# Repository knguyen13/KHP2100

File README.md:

# KHP2100

Description:
Interact with LEDs through mechanical switches.

Features a 2-layer board with a 5V LDO regulator, atmega328p MCU, push-buttons, leds, and supporting components.
Mode button with a hardware trigger(interrupt) to switch between different game modes. 
ICSP connection to MCU for reprogrammability.

Archived 02/08/2022

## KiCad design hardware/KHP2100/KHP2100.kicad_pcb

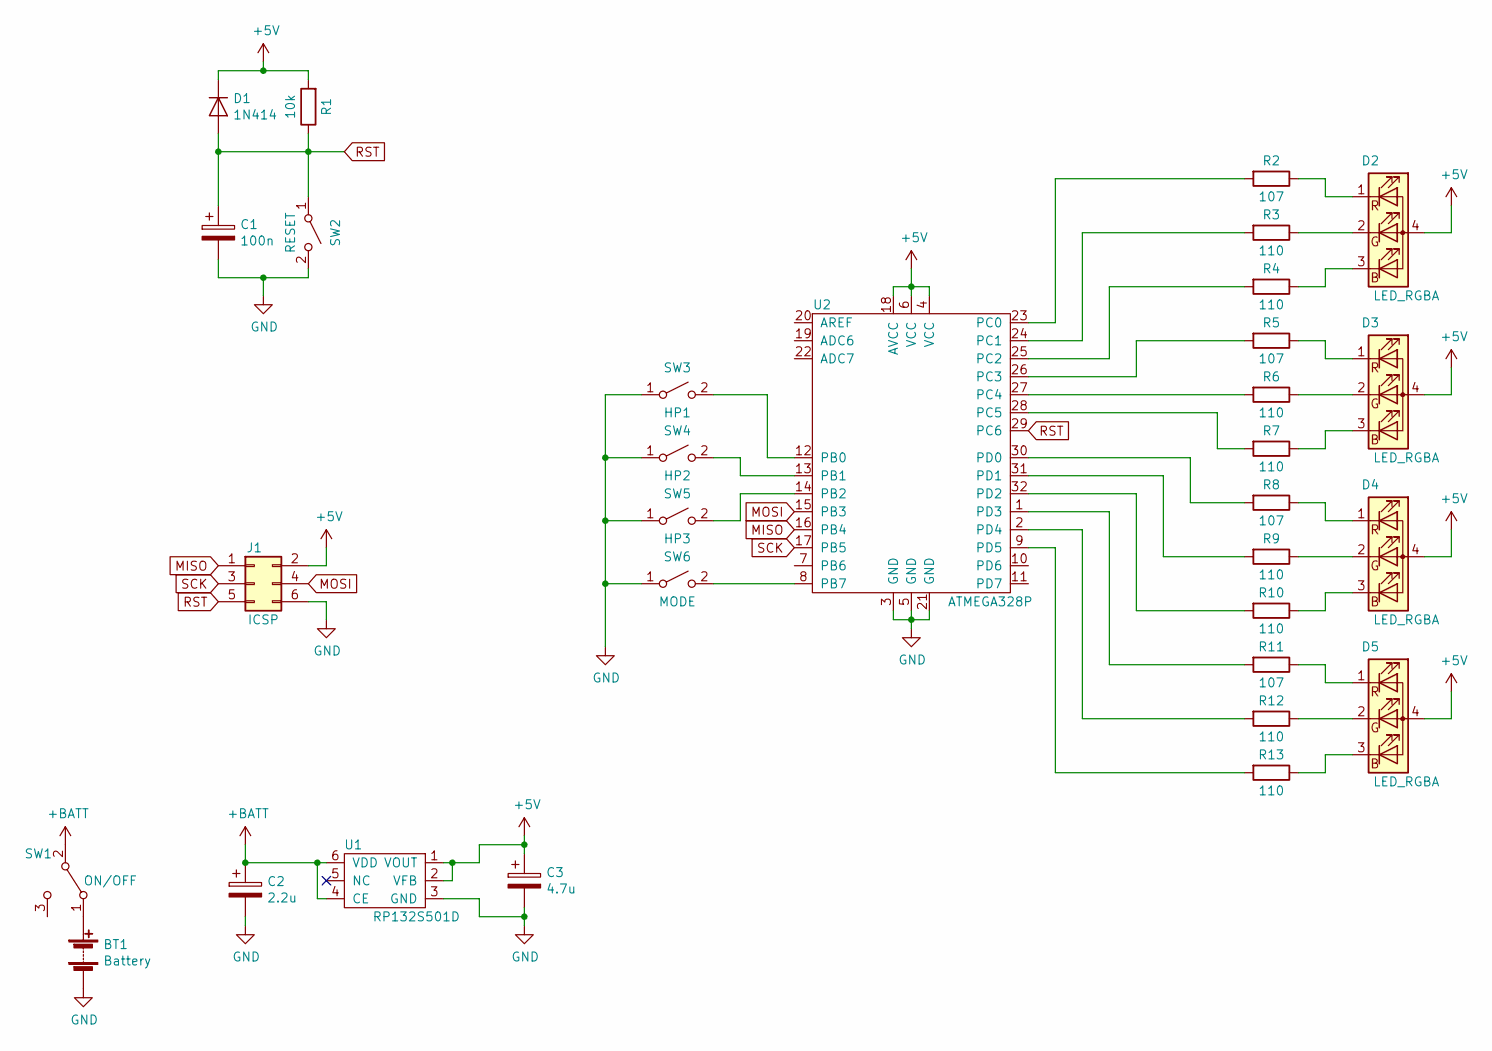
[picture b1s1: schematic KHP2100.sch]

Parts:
BT1: Battery; BH800S
C1: 100n; C_0603_1608Metric_Pad1.05x0.95mm_HandSolder
C2: 2.2u; C_0603_1608Metric_Pad1.05x0.95mm_HandSolder
C3: 4.7u; C_0603_1608Metric_Pad1.05x0.95mm_HandSolder
D1: 1N414; D_SOD-123
D2, D3, D4, D5: LED_RGBA; RGB_LED_0606_1616METRIC
J1: ICSP
R1: 10k; R_0603_1608Metric_Pad1.05x0.95mm_HandSolder
R2, R5, R8, R11: 107; R_1206_3216Metric_Pad1.42x1.75mm_HandSolder
R3, R4, R6, R7, R9, R10, R12, R13: 110; R_0805_2012Metric_Pad1.15x1.40mm_HandSolder
SW1: ON/OFF; CJS1200A
SW2: RESET; EVQ-Q2Y03W
SW3: HP1; MX_SWITCH
SW4: HP2; MX_SWITCH
SW5: HP3; MX_SWITCH
SW6: MODE; EVQ-Q2Y03W
U1: RP132S501D
U2: ATMEGA328P

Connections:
+5V: C3.1, D1.1 (K), D2.4 (A), D3.4 (A), D4.4 (A), D5.4 (A), J1.2, R1.2, U1.1 (VOUT), U1.2 (VFB), U2.4 (VCC), U2.6 (VCC), U2.18 (AVCC)
+BATT: C2.1, SW1.2 (B), U1.4 (CE), U1.6 (VDD); also elsewhere on the board
GND: BT1.2 (-), C1.2, C2.2, C3.2, J1.6, SW2.2 (B), SW3.1 (A), SW4.1 (A), SW5.1 (A), SW6.1 (A), U1.3 (GND), U2.3 (GND), U2.5 (GND), U2.21 (GND); also elsewhere on the board
MISO: J1.1, U2.16 (PB4)
MOSI: J1.4, U2.15 (PB3)
unnamed 5: BT1.1 (+), SW1.1 (A); also elsewhere on the board
unnamed: D2.1 (RK), R2.1
unnamed: D2.2 (GK), R3.1
unnamed: D2.3 (BK), R4.1
unnamed: D3.1 (RK), R5.1
unnamed: D3.2 (GK), R6.1
unnamed: D3.3 (BK), R7.1
unnamed: D4.1 (RK), R8.1
unnamed: D4.2 (GK), R9.1
unnamed: D4.3 (BK), R10.1
unnamed: D5.1 (RK), R11.1
unnamed: D5.2 (GK), R12.1
unnamed: D5.3 (BK), R13.1
unnamed: R2.2, U2.23 (PC0)
unnamed: R3.2, U2.24 (PC1)
unnamed: R4.2, U2.25 (PC2)
unnamed: R5.2, U2.26 (PC3)
unnamed: R6.2, U2.27 (PC4)
unnamed: R7.2, U2.28 (PC5)
unnamed: R8.2, U2.30 (PD0)
unnamed: R9.2, U2.31 (PD1)
unnamed: R10.2, U2.32 (PD2)
unnamed: R11.2, U2.1 (PD3)
unnamed: R12.2, U2.2 (PD4)
unnamed: R13.2, U2.9 (PD5)
unnamed: SW3.2 (B), U2.12 (PB0)
unnamed: SW4.2 (B), U2.13 (PB1)
unnamed: SW5.2 (B), U2.14 (PB2)
unnamed 34: SW6.2 (B), U2.8 (PB7); also elsewhere on the board
RST: C1.1, D1.2 (A), J1.5, R1.1, SW2.1 (A), U2.29 (PC6); also elsewhere on the board
SCK: J1.3, U2.17 (PB5)

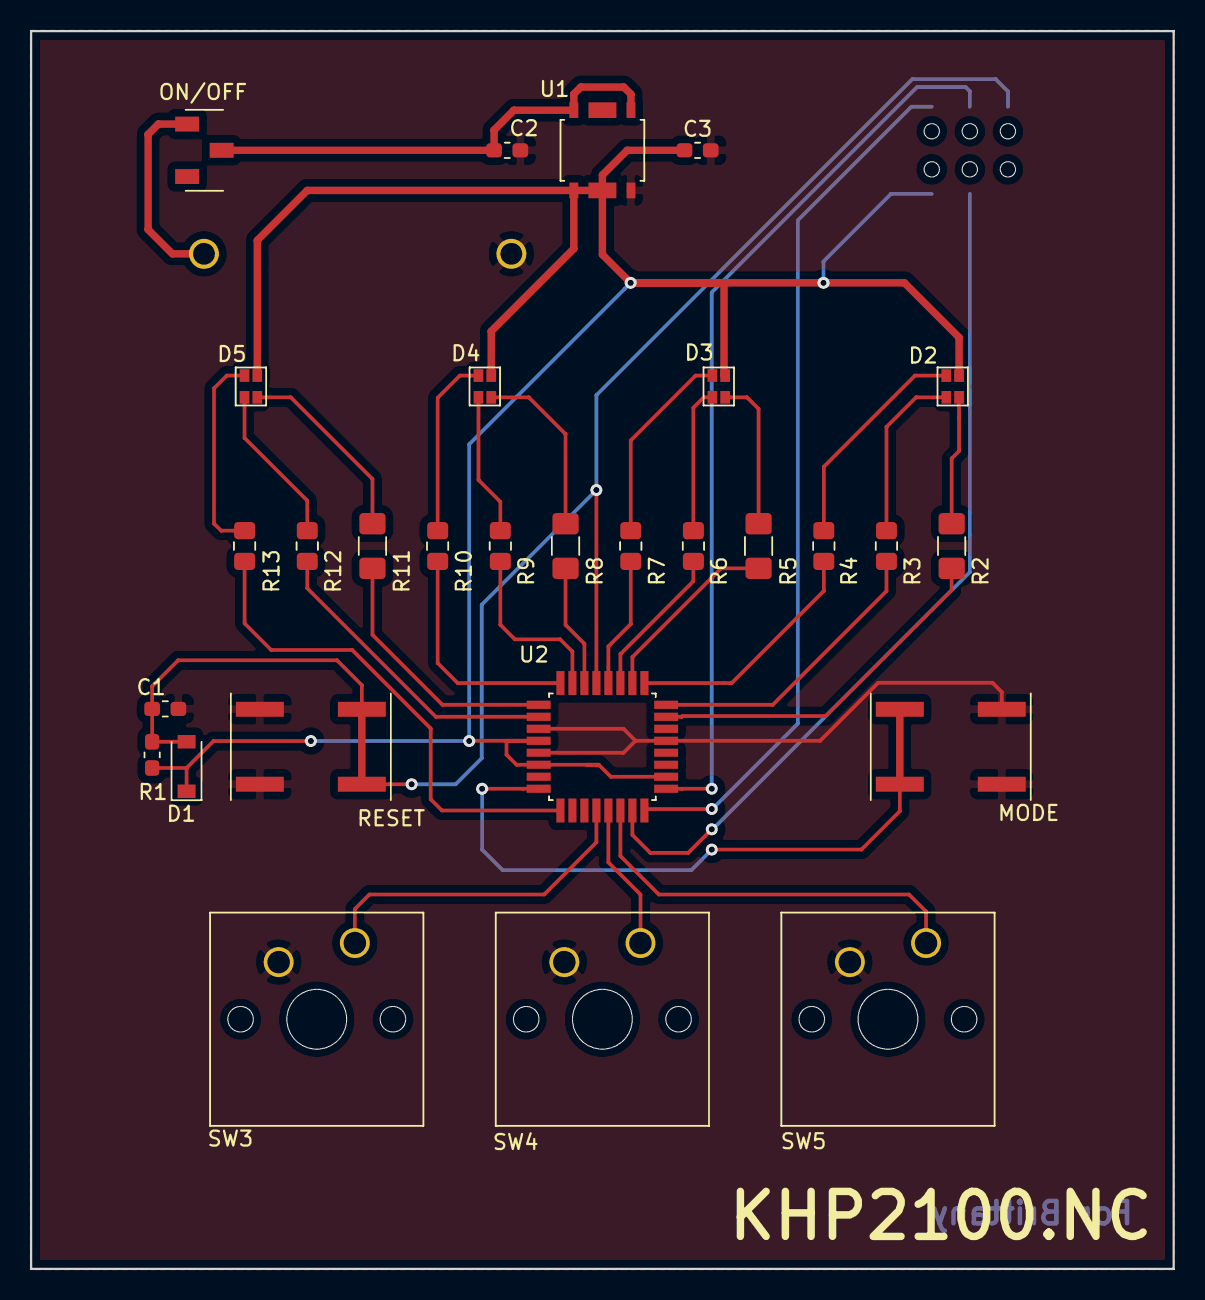
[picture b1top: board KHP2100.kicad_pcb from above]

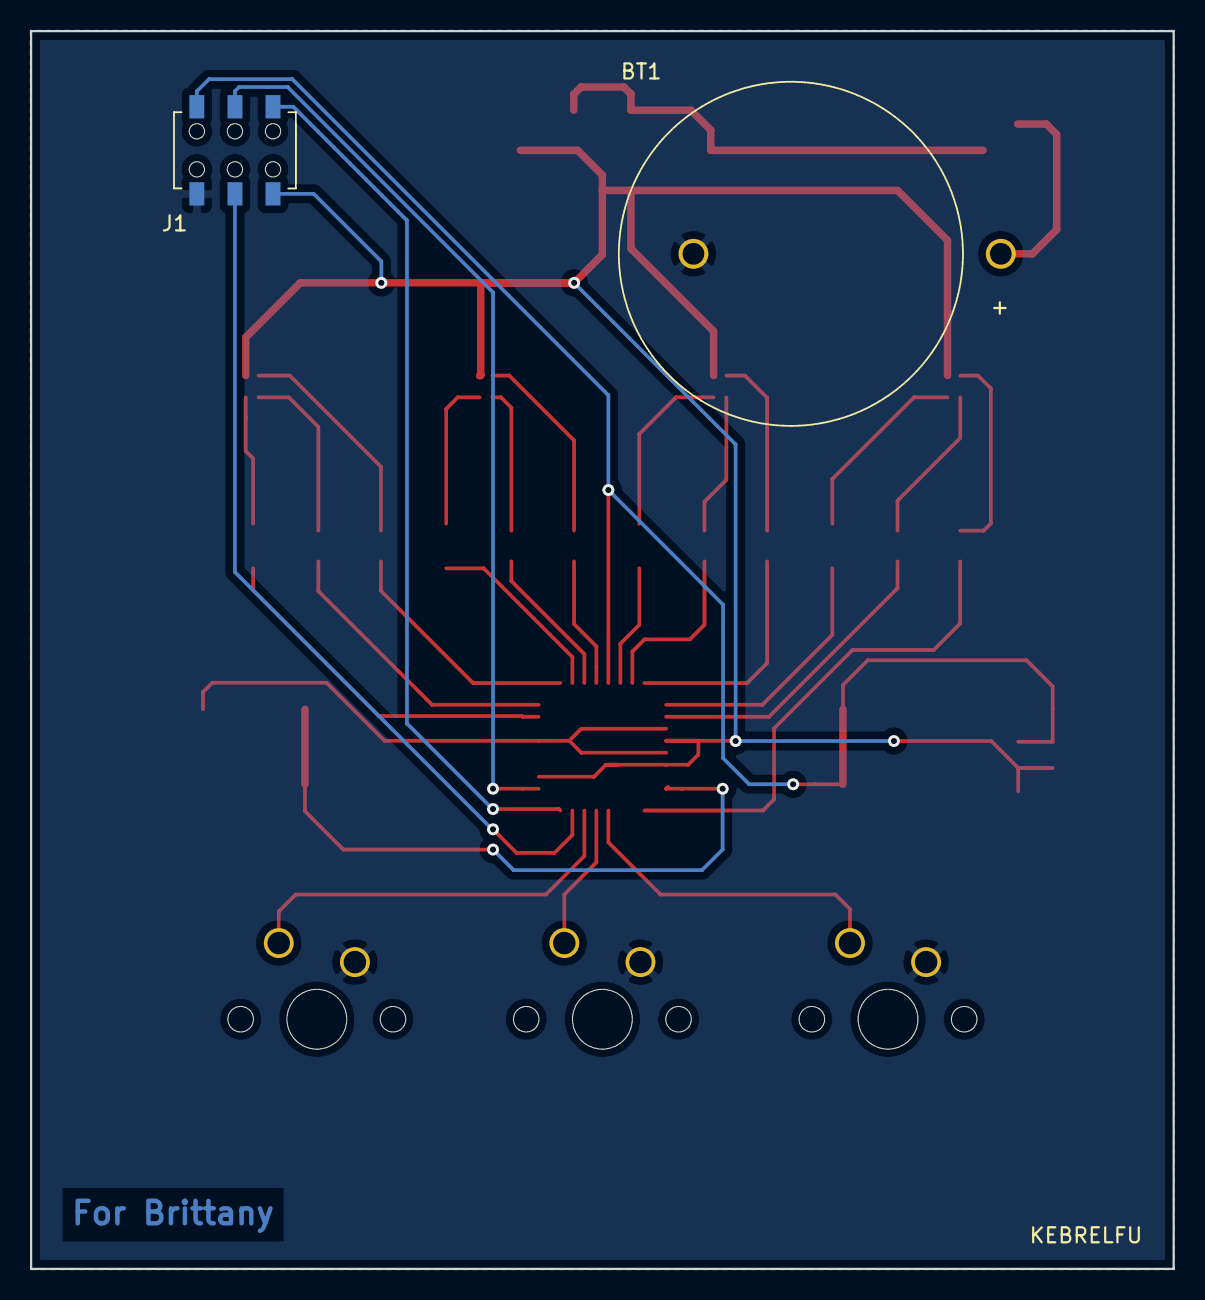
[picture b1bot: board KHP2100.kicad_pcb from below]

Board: 2 copper layers, 76.2 x 82.6 mm, 31 parts (2 on the bottom side), 36 nets.

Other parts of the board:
MODE: MODE; EVQ-Q2Y03W
ON/OFF: ON/OFF; CJS1200A
RESET: RESET; EVQ-Q2Y03W

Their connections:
+BATT: ON/OFF.2; also elsewhere on the board
GND: MODE.1, RESET.2; also elsewhere on the board
unnamed 5: ON/OFF.1; also elsewhere on the board
unnamed 34: MODE.2; also elsewhere on the board
RST: RESET.1; also elsewhere on the board

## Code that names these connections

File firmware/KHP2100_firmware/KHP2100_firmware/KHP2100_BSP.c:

/*
Board Support Package for KHP2100_firmware
*/

#include <avr/io.h>
#include <util/delay.h>
#include "KHP2100_BSP.h"

uint8_t selected_mode = 0;
uint8_t last_mode = 4;
// game 1 
uint8_t butt_status = 0;
// game 3
uint8_t bomb = 3;
uint8_t mine_1 = 1;
uint8_t mine_2 = 1;
uint8_t mine_3 = 1;

// function portb_init configures PB0, PB1, PB2, PB7 as digital inputs with pull up resistors
void portb_init(void) {
	DDRB &= (0 << PINB0) | (0 << PINB1) | (0 << PINB2) | (0 << PINB7); // set as digital inputs
	PORTB |= (1 << PINB0) | (1 << PINB1) | (1 << PINB2) | (1 << PINB7); // enable pull up resistors
} // end function portb_init

// function portc_init configures PC0, PC1, PC2 as digital outputs 
void portc_init(void) {
	DDRC |= (1 << PINC0) | (1 << PINC1) | (1 << PINC2) | (1 << PINC3) | (1 << PINC4) | (1 << PINC5); // set as digital outputs
	PORTC |= (1 << PINC0) | (1 << PINC1) | (1 << PINC2) | (1 << PINC3) | (1 << PINC4) | (1 << PINC5); // initialize to HIGH
} // end function portc_init

// function portd_init configures PD0, PD1, PD2 as digital outputs
void portd_init(void) {
	DDRD |= (1 << PIND0) | (1 << PIND1) | (1 << PINC2); // set as digital outputs
	PORTD |= (1 << PIND0) | (1 << PIND1) | (1 << PIND2); // initialize to HIGH
} // end function portd_init

// function mode_init(void) configures PB7 as interrupt
void interrupt_init(void) {
	PCICR |= (1 << 0);
	PCMSK0 |= (1 << PCINT7);
} // end function mode_init

// function delay prevents switch bounce
void debounce(void) {
	_delay_ms(100);
} // end function delay

uint8_t read_Button(void) {
	return (PINB & 0x07);
}

// function control_LED
void control_LED(uint8_t light, uint8_t color) {
	if (light == 0) { // D2
		PORTC |= 0x07; // clear PC0, PC1, PC2
		PORTC &= 0xF8 + color; // insert new value for PC0, PC1, PC2
	} else if (light == 1) { // D3
		PORTC |= 0x38; // clear PC3, PC4, PC5
		PORTC &= 0x07 + (color << 3); // insert new value for PC3, PC4, PC5
	} else if (light == 2) { // D4
		PORTD |= 0x07; // clear PD0, PD1, PD2
		PORTD &= color; // insert new value for PD0, PD1, PD2
	} else { // all LEDS
		// clear all LEDS and insert new values
		PORTC |= 0xFF;
		PORTC &= color + (color << 3);
		PORTD |= 0x07;
		PORTD &= color;
	} // end if-else
} // end function control_LED

// function mode_0 shines the LEDs in a pattern
void mode_0(void) {
	start_sequence(0);
	if ((read_Button() & 0x7) != 0x7) {
		butt_status = read_Button() & 0x7;
	}
	if (butt_status == 0x3) {
		light_show_2();
	} else if (butt_status == 0x5) {
		light_show_1();
	} else {
		light_show_0();
	}
} // end function mode_0

// function mode_1 allows the user to control the LED through the push button's
void mode_1(void) {
	start_sequence(1);
	switch(read_Button()) {
		case 0x01:
			control_LED(ALL, CYAN);
			break;
		case 0x02:
			control_LED(ALL, MAGENTA);
			break;
		case 0x03:
			control_LED(ALL, BLUE);
			break;
		case 0x04:
			control_LED(ALL, YELLOW);
			break;
		case 0x05:
			control_LED(ALL, GREEN);
			break;
		case 0x06:
			control_LED(ALL, RED);
			break;
		case 0x00:
			control_LED(ALL, WHITE);
			break;
		default:
			control_LED(ALL, OFF);// turn off PC0, PC1, PC2
	} // end switch
	debounce();
} // end function mode_1

// function mode_2, one led/switch pair is bomb. press wrong one and the LED's turn red.
void mode_2(void) {
	start_sequence(2);
	if(bomb == 3) {
		bomb = srand(read_Button()) % 3;
	}
	if ((mine_1 == 1) && (mine_2 == 1) && (mine_3 == 1)) {
		bomb = rand() % 3;
		control_LED(ALL, OFF);
		control_LED(ALL, BLUE);
		_delay_ms(200);
		control_LED(ALL, OFF);
		control_LED(ALL, CYAN);
		mine_1 = 0;
		mine_2 = 0;
		mine_3 = 0;
	} 
	switch((read_Button() & 0x7)) {
		case 0x6:
			control_LED(D4, OFF);
			if(bomb == 0) {
				control_LED(D4, RED);
			} else {
				control_LED(D4, GREEN);
			} // end if-else
			mine_1 = 1;
			_delay_ms(500);
			break;
		case 0x5:
			control_LED(D3, OFF);
			if(bomb == 1) {
				control_LED(D3, RED);
			} else {
				control_LED(D3, GREEN);
			} // end if-else
			mine_2 = 1;
			_delay_ms(500);
			break;
		case 0x3:
			control_LED(D2, OFF);
			if(bomb == 2) {
				control_LED(D2, RED);								
			} else {
				control_LED(D2, GREEN);
			} // end if-else
			mine_3 = 1;
			_delay_ms(500);
			break;
	} // end switch case
} // end function mode_2

// function start_sequence 
void start_sequence(uint8_t mode_num) {
	if(last_mode != selected_mode) {
		for(int i = 0; i < 2; ++i) {
			switch(mode_num) {
				case 0: 
				control_LED(ALL, RED);
				break;
				case 1:
				control_LED(ALL, GREEN);
				break;
				case 2:
				control_LED(ALL, BLUE);
				break;
				case 3:
				control_LED(ALL, YELLOW);
				break;
			} // end  switch case
			_delay_ms(500);
			control_LED(ALL, OFF);
			_delay_ms(500);
		} // end for
	} // end if
} // end function start_sequence

void light_show_0(void) {
	control_LED(D4, RED);
	_delay_ms(100);
	control_LED(ALL, OFF);
	control_LED(D3, YELLOW);
	_delay_ms(100);
	control_LED(ALL, OFF);
	control_LED(D2, GREEN);
	_delay_ms(100);
	control_LED(ALL, OFF);
	control_LED(D3, CYAN);
	_delay_ms(100);
	control_LED(ALL, OFF);
	control_LED(D4, BLUE);
	_delay_ms(100);
	control_LED(ALL, OFF);
	control_LED(D3, MAGENTA);
	_delay_ms(100);
	control_LED(ALL, OFF);
	control_LED(D2, RED);
	_delay_ms(100);
	control_LED(ALL, OFF);
	control_LED(D3, YELLOW);
	_delay_ms(100);
	control_LED(ALL, OFF);
	control_LED(D4, GREEN);
	_delay_ms(100);
	control_LED(ALL, OFF);
	control_LED(D3, CYAN);
	_delay_ms(100);
	control_LED(ALL, OFF);
	control_LED(D2, BLUE);
	_delay_ms(100);
	control_LED(ALL, OFF);
	control_LED(D3, MAGENTA);
	_delay_ms(100);
	control_LED(ALL, OFF);
}

void light_show_1(void) {
	control_LED(ALL, RED);
	_delay_ms(1000);
	control_LED(ALL,OFF);
	control_LED(ALL, YELLOW);
	_delay_ms(1000);
	control_LED(ALL,OFF);
	control_LED(ALL, GREEN);
	_delay_ms(1000);
	control_LED(ALL,OFF);
	control_LED(ALL, CYAN);
	_delay_ms(1000);
	control_LED(ALL,OFF);
	control_LED(ALL, BLUE);
	_delay_ms(1000);
	control_LED(ALL,OFF);
	control_LED(ALL, MAGENTA);
	_delay_ms(1000);
	control_LED(ALL,OFF);
	control_LED(ALL, WHITE);
	_delay_ms(1000);
	control_LED(ALL,OFF);
}

void light_show_2(void) {
	control_LED(D2, RED);
	_delay_ms(150);
	control_LED(ALL, OFF);
	control_LED(D3, WHITE);
	_delay_ms(150);
	control_LED(ALL, OFF);
	control_LED(D4, BLUE);
	_delay_ms(150);
	control_LED(ALL,OFF);
}

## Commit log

2021-01-18 Add files via upload
    pcb design files
2021-01-18 Create firmware
